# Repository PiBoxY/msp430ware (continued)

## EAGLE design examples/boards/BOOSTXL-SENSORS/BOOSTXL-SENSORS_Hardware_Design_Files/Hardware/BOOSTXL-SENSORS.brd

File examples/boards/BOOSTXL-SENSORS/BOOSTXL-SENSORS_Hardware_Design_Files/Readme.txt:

BOOSTXL-SENSORS Hardware Design Files v1.00.00
Texas Instruments, Inc.

********************************************************************************
Welcome to the BOOSTXL-SENSORS BoosterPack!
********************************************************************************

In this package, you will find hardware design files that can help you quickly
get started on developing your own project.

Available in the 'Hardware' folder are the complete board schematic and layout,
bill of material, and Gerber files.

You can also find various web links in the 'Documentation' folder pointing to
the Tool Page, Quick Start Guide, and User's Guide.

For more resources, be sure to visit www.ti.com/tool/boostxl-sensors

********************************************************************************
Revision History
********************************************************************************
Ver 1.00.00 - June 3rd, 2016
- Initial Release

********************************************************************************
Project File Listing
********************************************************************************
|--Documentation                      : Folder containing links to more resources
|--Hardware                           : Folder containing hardware design files,
                                        bill of material and gerber files
|--Readme.txt                         : This file

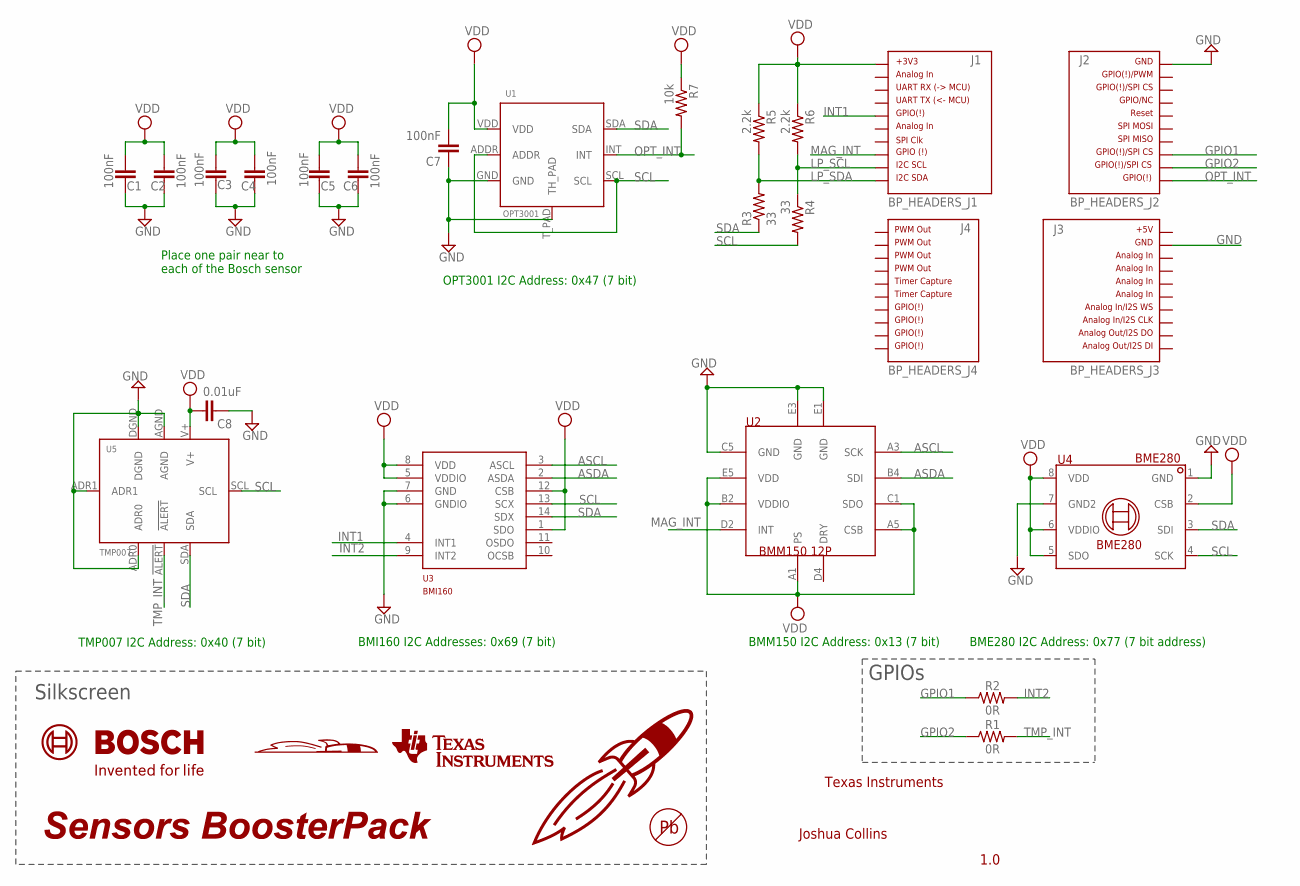
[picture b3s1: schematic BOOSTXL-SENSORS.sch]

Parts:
C1, C2, C3, C4, C5, C6, C7: 100nF; 0402-CAP
C8: 0.01uF; 0402-CAP
J1: BP_HEADERS_J1; J1
J2: BP_HEADERS_J2; J2
J3: BP_HEADERS_J3; J3
J4: BP_HEADERS_J4; J4
R1, R2: 0R; 0603
R3, R4: 33; 0402-RES
R5, R6: 2.2k; 0402-RES
R7: 10k; 0402-RES
U1: OPT3001; OPT3001DNP
U2: BMM150; WLCSP12_1.56X1.56
U3: BMI160; LGA12_2.5X3.0
U4: BME280; LGA8_2.5X2.5
U5: TMP007; TMP007AIYZF
U$1: BOSCH_LOGO_BOTTOM
U$2: HALF_ROCKET_BOTTOM_SILK; HALF_ROCKET_LG
U$3: ROCKET_45_MED_TOP_SILK
U$4: SENSORS_BP_TOP_SILK; SENSORS_BP
U$5: TI_LOGO_LG_BOTTOM_SILK; TI_LOGO_BOTTOMSILK
U$6: PB-FREE

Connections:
ASCL: U2.A3 (SCK), U3.3 (ASCL)
ASDA: U2.B4 (SDI), U3.2 (ASDA)
GND: C1.1, C2.1, C3.1, C4.1, C5.1, C6.1, C7.1, C8.1, J2.20, J3.22, U1.GND, U1.T_PAD (TH_PAD), U2.C5 (GND), U2.E1 (GND), U2.E3 (GND), U3.6 (GNDIO), U3.7 (GND), U4.1 (GND), U4.7 (GND2), U5.ADR0, U5.ADR1, U5.AGND, U5.DGND
GPIO1: J2.13, R2.1
GPIO2: J2.12, R1.1
INT1: J1.5, U3.4 (INT1)
INT2: R2.2, U3.9 (INT2)
LP_SCL: J1.9, R4.1, R6.2
LP_SDA: J1.10, R3.2, R5.2
MAG_INT: J1.8, U2.D2 (INT)
OPT_INT: J2.11, R7.2, U1.INT
SCL: R4.2, U1.ADDR, U1.SCL, U3.13 (SCX), U4.4 (SCK), U5.SCL
SDA: R3.1, U1.SDA, U3.14 (SDX), U4.3 (SDI), U5.SDA
TMP_INT: R1.2, U5.!ALERT
VDD: C1.2, C2.2, C3.2, C4.2, C5.2, C6.2, C7.2, C8.2, J1.1, R5.1, R6.1, R7.1, U1.VDD, U2.A1 (PS), U2.A5 (CSB), U2.B2 (VDDIO), U2.C1 (SDO), U2.E5 (VDD), U3.1 (SDO), U3.5 (VDDIO), U3.8 (VDD), U3.12 (CSB), U4.2 (CSB), U4.5 (SDO), U4.6 (VDDIO), U4.8 (VDD), U5.V+

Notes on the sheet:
BMI160 I2C Addresses: 0x69 (7 bit)
BMM150 I2C Address: 0x13 (7 bit)
BME280 I2C Address: 0x77 (7 bit address)
Place one pair near to each of the Bosch sensor
TMP007 I2C Address: 0x40 (7 bit)
OPT3001 I2C Address: 0x47 (7 bit)
Silkscreen
Texas Instruments
Joshua Collins
1.0
GPIOs

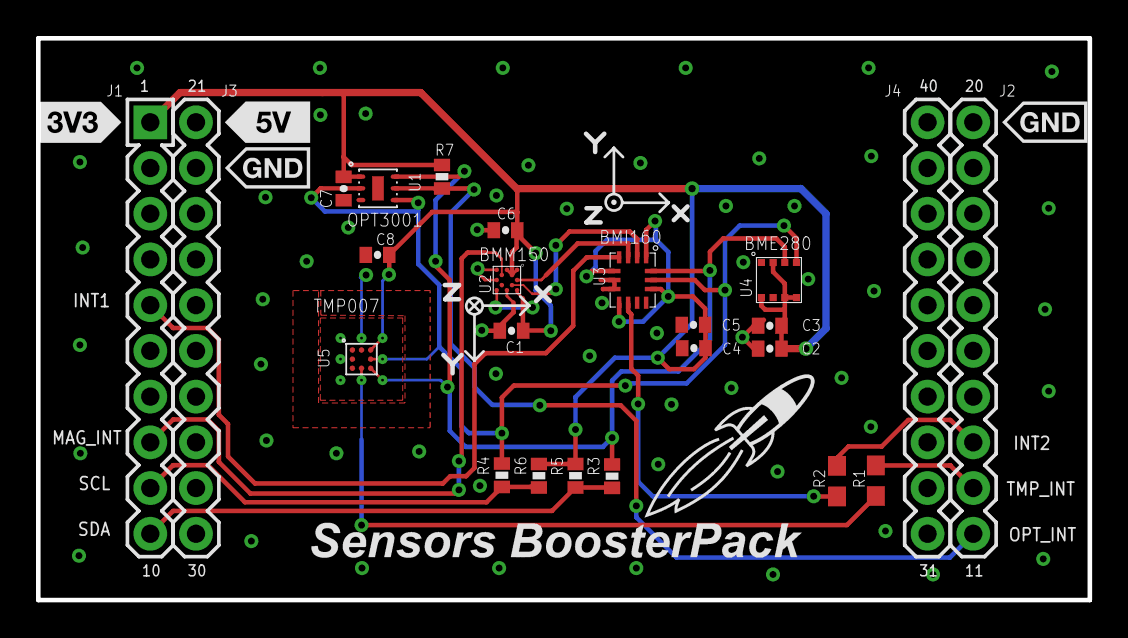
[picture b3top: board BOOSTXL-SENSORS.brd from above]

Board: 2 copper layers, 58.4 x 31.2 mm, 30 parts (0 on the bottom side), 15 nets.

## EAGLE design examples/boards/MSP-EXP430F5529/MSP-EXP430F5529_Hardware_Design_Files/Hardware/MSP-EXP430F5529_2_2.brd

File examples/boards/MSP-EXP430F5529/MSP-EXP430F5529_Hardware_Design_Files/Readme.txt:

MSP-EXP430F5529 Experimenter's Board Hardware Design Files v1.40.00
Texas Instruments, Inc.

********************************************************************************
Welcome to the MSP-EXP430F5529 Experimenter's Board!
********************************************************************************

In this package, you will find hardware design files that can help you quickly
get started on developing your own project.

Available in the 'Hardware' folder are the complete board schematic and layout,
bill of material and Gerber files.

You can also find various web links in the 'Documentation' folder pointing to
the LaunchPad's Homepage, Quick Start Guide, and User's Guide.

For more resources, be sure to visit www.ti.com/tool/msp-exp430f5529

********************************************************************************
Revision History
********************************************************************************
Ver 1.40.00 - August 24th, 2015
- Added new hardware Rev2.2 design files
- Updated User Experience demo to work with new replacement accelerometer

********************************************************************************
Project File Listing
********************************************************************************
|--Documentation                      : Folder containing links to more resources
|--Hardware                           : Folder containing hardware design files,
                                        bill of material and gerber files
|--Readme.txt                         : This file

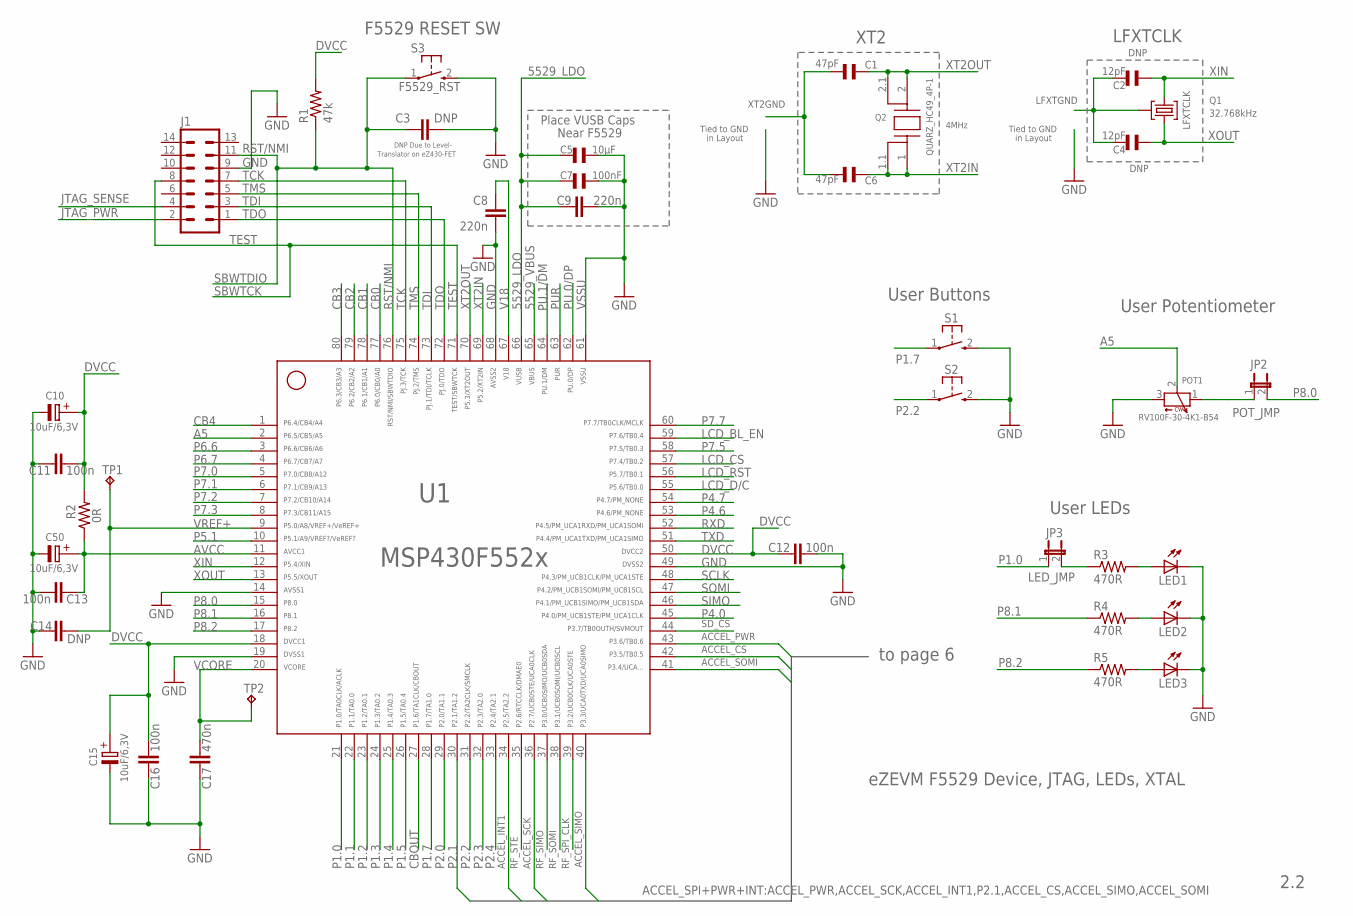
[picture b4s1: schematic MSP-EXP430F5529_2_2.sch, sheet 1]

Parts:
C1, C6: 47pF; CSMD0805
C2, C4: 12pF; CSMD0805
C3, C14: DNP; C0603
C5: 10µF; CSMD0805
C7: 100nF; CSMD0805
C8, C9: 220n; C0603
C10, C15, C50: 10uF/6,3V; 1210ELKO
C11: 100n; C0603
C12, C13, C16: 100n; C0805
C17: 470n; C0805
J1: ML14
JP2: POT_JMP; JP1S
JP3: LED_JMP; JP1S
LED1, LED2, LED3: LEDCHIPLED_0603; CHIPLED_0603
POT1: RV100F-30-4K1-B54; TW-700171
Q1: 32.768kHz; F20XX_PIR_DEMO_&_EVAL_CMJ206T
Q2: QUARZ_HC49_4P-1; QUARZ_HC49_4P
R1: 47k; R0603
R2: 0R; R0603
R3, R4, R5: 470R; R0603
S1, S2: PB; PBTH
S3: F5529_RST; PBTH
TP1, TP2: TP
U1: MSP430F5529IPNR; PN80

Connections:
5529_LDO: C5.1, C7.1, C9.1, U1.66; also elsewhere on the board
5529_VBUS: U1.65; also elsewhere on the board
A5: POT1.2 (TAP), U1.2
ACCEL_CS: U1.42; also elsewhere on the board
ACCEL_INT1: U1.34; also elsewhere on the board
ACCEL_PWR: U1.43; also elsewhere on the board
ACCEL_SCK: U1.36; also elsewhere on the board
ACCEL_SIMO: U1.40; also elsewhere on the board
ACCEL_SOMI: U1.41; also elsewhere on the board
AVCC: C13.1, C50.+, R2.1, U1.11
CB0: U1.77; also elsewhere on the board
CB1: U1.78; also elsewhere on the board
CB2: U1.79; also elsewhere on the board
CB3: U1.80; also elsewhere on the board
CB4: U1.1; also elsewhere on the board
CBOUT: U1.27; also elsewhere on the board
DVCC: C10.+, C11.2, C12.1, C15.+, C16.2, R1.2, R2.2, U1.18, U1.50; also elsewhere on the board
GND: C3.1, C5.2, C7.2, C8.2, C9.2, C10.-, C11.1, C12.2, C13.2, C14.1, C15.-, C16.1, C17.1, C50.-, J1.9, LED1.C, LED2.C, LED3.C, POT1.3 (CW), S1.2 (S), S2.2 (S), S3.2 (S), U1.14, U1.19, U1.49, U1.61, U1.68; also elsewhere on the board
JTAG_PWR: J1.2; also elsewhere on the board
JTAG_SENSE: J1.4; also elsewhere on the board
LCD_BL_EN: U1.59; also elsewhere on the board
LCD_CS: U1.57; also elsewhere on the board
LCD_D/C: U1.55; also elsewhere on the board
LCD_RST: U1.56; also elsewhere on the board
LFXTGND: C2.2, C4.2, Q1.P3 (GND)
unnamed: LED3.A, R5.2
unnamed: LED1.A, R3.2
unnamed: LED2.A, R4.2
unnamed: JP3.2, R3.1
unnamed: JP2.1, POT1.1 (CCW)
P1.0: JP3.1, U1.21; also elsewhere on the board
P1.1: U1.22; also elsewhere on the board
P1.2: U1.23; also elsewhere on the board
P1.3: U1.24; also elsewhere on the board
P1.4: U1.25; also elsewhere on the board
P1.5: U1.26; also elsewhere on the board
P1.7: S1.1, U1.28
P2.0: U1.29; also elsewhere on the board
P2.1: U1.30; also elsewhere on the board
P2.2: S2.1, U1.31
P2.3: U1.32; also elsewhere on the board
P2.4: U1.33; also elsewhere on the board
P4.0: U1.45; also elsewhere on the board
P4.6: U1.53; also elsewhere on the board
P4.7: U1.54; also elsewhere on the board
P5.1: U1.10; also elsewhere on the board
P6.6: U1.3; also elsewhere on the board
P6.7: U1.4; also elsewhere on the board
P7.0: U1.5; also elsewhere on the board
P7.1: U1.6; also elsewhere on the board
P7.2: U1.7; also elsewhere on the board
P7.3: U1.8; also elsewhere on the board
P7.5: U1.58; also elsewhere on the board
P7.7: U1.60; also elsewhere on the board
P8.0: JP2.2, U1.15; also elsewhere on the board
P8.1: R4.1, U1.16; also elsewhere on the board
P8.2: R5.1, U1.17; also elsewhere on the board
PU.0/DP: U1.62; also elsewhere on the board
PU.1/DM: U1.64; also elsewhere on the board
PUR: U1.63; also elsewhere on the board
RF_SIMO: U1.37; also elsewhere on the board
RF_SOMI: U1.38; also elsewhere on the board
RF_SPI_CLK: U1.39; also elsewhere on the board
RF_STE: U1.35; also elsewhere on the board
RST/NMI: C3.2, J1.11, R1.1, S3.1, U1.76; also elsewhere on the board
RXD: U1.52; also elsewhere on the board
SCLK: U1.48; also elsewhere on the board
SD_CS: U1.44; also elsewhere on the board
SIMO: U1.46; also elsewhere on the board
SOMI: U1.47; also elsewhere on the board
TCK: J1.7, U1.75
TDI: J1.3, U1.73
TDO: J1.1, U1.72
TEST: J1.8, U1.71; also elsewhere on the board
TMS: J1.5, U1.74
TXD: U1.51; also elsewhere on the board
V18: C8.1, U1.67
VCORE: C17.2, TP2.1, U1.20
VREF+: C14.2, TP1.1, U1.9
XIN: C2.1, Q1.P2 (2), U1.12
XOUT: C4.1, Q1.P1 (1), U1.13
XT2GND: C1.2, C6.2
XT2IN: C6.1, Q2.1, Q2.1.1, U1.69
XT2OUT: C1.1, Q2.2, Q2.2.1, U1.70

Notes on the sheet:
4MHz
eZEVM F5529 Device, JTAG, LEDs, XTAL
LFXTCLK
DNP
SBWTDIO
SBWTCK
VSSU
2.2
Place VUSB Caps
Near F5529
F5529 RESET SW
DNP Due to Level-
Translator on eZ430-FET
User LEDs
User Buttons
User Potentiometer
XT2
Tied to GND
in Layout
to page 6

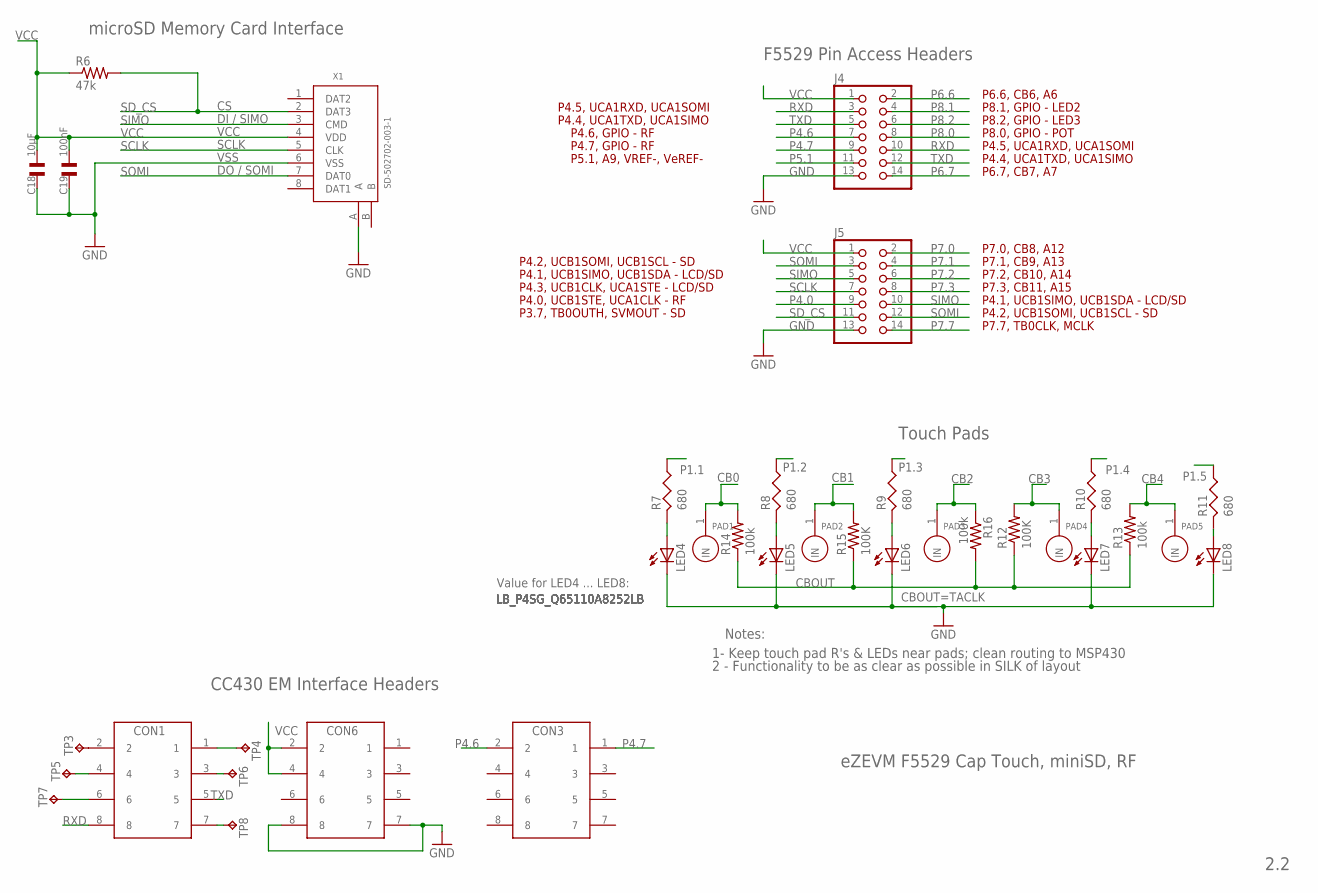
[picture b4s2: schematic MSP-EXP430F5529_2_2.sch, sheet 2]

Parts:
C18: 10µF; CSMD0805
C19: 100nF; CSMD0805
CON1, CON2, CON3: 8PIN_SM_MA_HEADER
J4, J5: PINHD-2X7; 2X07
LED4, LED5, LED6, LED7, LED8: LB_P4SG_Q65110A8252LB; LB_P4SG_Q65110A8252
PAD1, PAD2, PAD3, PAD4, PAD5: TPAD_TOPLB_P4SG; PAD_10X10_LB_P4SG
R6: 47k; R0603
R7, R8, R9, R10, R11: 680; R0805
R12, R15: 100K; R0603
R13, R14, R16: 100k; R0603
TP3, TP4, TP5, TP6, TP7, TP8: TP
X1: SD-502702-003-1; SD-502702-003

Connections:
CB0: PAD1.1, R14.2; also elsewhere on the board
CB1: PAD2.1, R15.2; also elsewhere on the board
CB2: PAD3.1, R16.1; also elsewhere on the board
CB3: PAD4.1, R12.2; also elsewhere on the board
CB4: PAD5.1, R13.2; also elsewhere on the board
CBOUT: R12.1, R13.1, R14.1, R15.1, R16.2; also elsewhere on the board
GND: C18.1, C19.1, CON2.7, CON2.8, J4.13, J5.13, LED4.C, LED5.C, LED6.C, LED7.C, LED8.C, X1.6 (VSS), X1.A; also elsewhere on the board
unnamed: LED7.A, R10.2
unnamed: LED5.A, R8.2
unnamed: LED6.A, R9.2
unnamed: LED4.A, R7.2
unnamed: CON1.6, TP7.1
unnamed: LED8.A, R11.2
unnamed: CON1.4, TP5.1
unnamed: CON1.2, TP3.1
unnamed: CON1.1, TP4.1
unnamed: CON1.3, TP6.1
unnamed: CON1.7, TP8.1
P1.1: R7.1; also elsewhere on the board
P1.2: R8.1; also elsewhere on the board
P1.3: R9.1; also elsewhere on the board
P1.4: R10.1; also elsewhere on the board
P1.5: R11.1; also elsewhere on the board
P4.0: J5.9; also elsewhere on the board
P4.6: CON3.2, J4.7; also elsewhere on the board
P4.7: CON3.1, J4.9; also elsewhere on the board
P5.1: J4.11; also elsewhere on the board
P6.6: J4.2; also elsewhere on the board
P6.7: J4.14; also elsewhere on the board
P7.0: J5.2; also elsewhere on the board
P7.1: J5.4; also elsewhere on the board
P7.2: J5.6; also elsewhere on the board
P7.3: J5.8; also elsewhere on the board
P7.7: J5.14; also elsewhere on the board
P8.0: J4.8; also elsewhere on the board
P8.1: J4.4; also elsewhere on the board
P8.2: J4.6; also elsewhere on the board
RXD: CON1.8, J4.3, J4.10; also elsewhere on the board
SCLK: J5.7, X1.5 (CLK); also elsewhere on the board
SD_CS: J5.11, R6.2, X1.2 (DAT3); also elsewhere on the board
SIMO: J5.5, J5.10, X1.3 (CMD); also elsewhere on the board
SOMI: J5.3, J5.12, X1.7 (DAT0); also elsewhere on the board
TXD: CON1.5, J4.5, J4.12; also elsewhere on the board
VCC: C18.2, C19.2, CON2.2, CON2.4, J4.1, J5.1, R6.1, X1.4 (VDD); also elsewhere on the board

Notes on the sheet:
eZEVM F5529 Cap Touch, miniSD, RF
CON1
CON3
CON6
CC430 EM Interface Headers
microSD Memory Card Interface
DI / SIMO
DO / SOMI
SCLK
VCC
VSS
2.2
Touch Pads
Notes:
1- Keep touch pad R's & LEDs near pads; clean routing to MSP430
2 - Functionality to be as clear as possible in SILK of layout
CBOUT=TACLK
F5529 Pin Access Headers
P7.0, CB8, A12
P7.1, CB9, A13
P7.2, CB10, A14
P7.3, CB11, A15
P4.1, UCB1SIMO, UCB1SDA - LCD/SD
P7.7, TB0CLK, MCLK
P8.1, GPIO - LED2
P8.2, GPIO - LED3
P4.5, UCA1RXD, UCA1SOMI
P6.7, CB7, A7
P4.4, UCA1TXD, UCA1SIMO
P5.1, A9, VREF-, VeREF-
P4.6, GPIO - RF
P4.7, GPIO - RF
P4.3, UCB1CLK, UCA1STE - LCD/SD
P4.2, UCB1SOMI, UCB1SCL - SD
P4.0, UCB1STE, UCA1CLK - RF
P3.7, TB0OUTH, SVMOUT - SD
P6.6, CB6, A6
P8.0, GPIO - POT
Value for LED4 ... LED8:

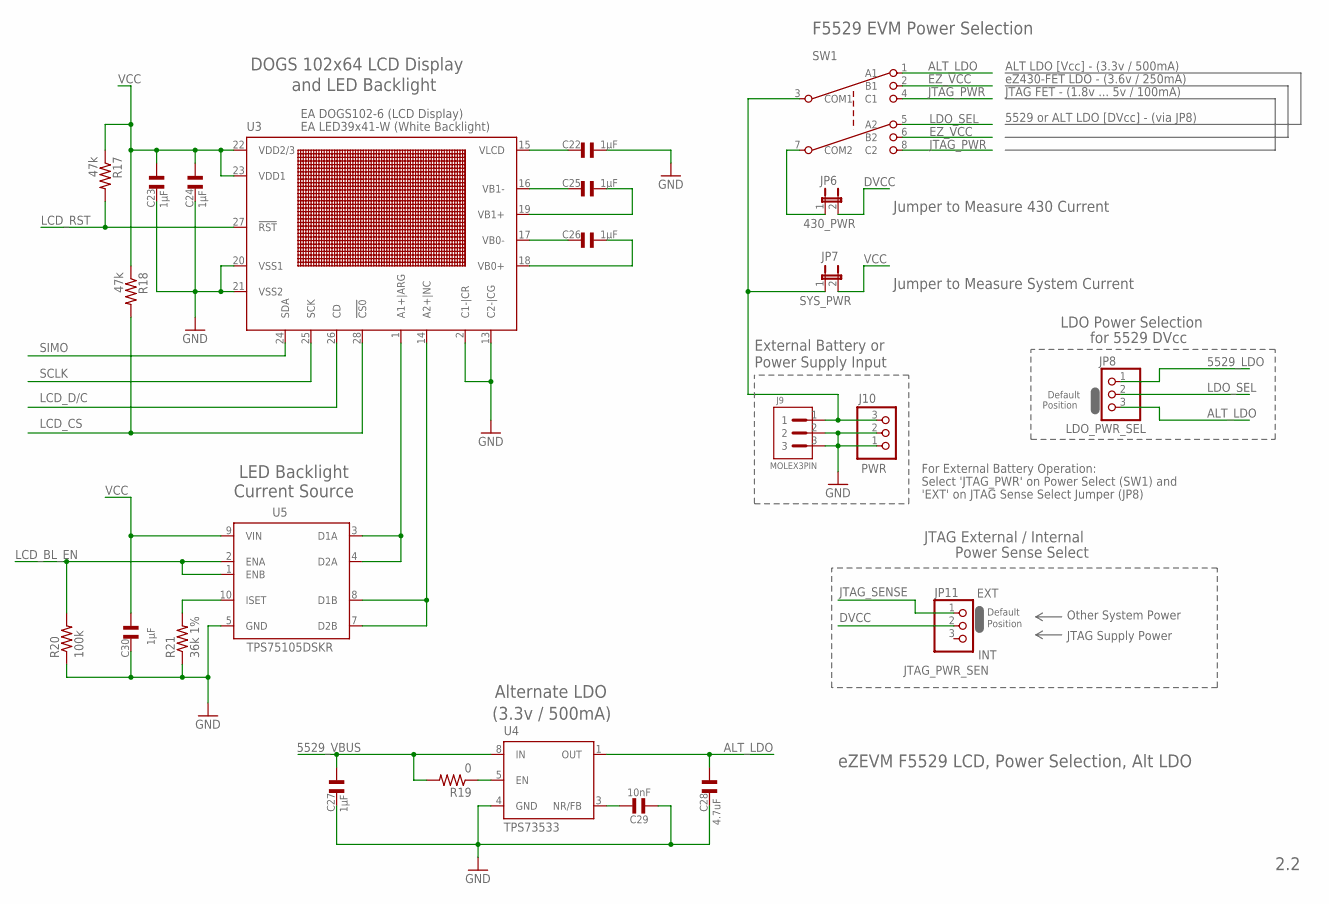
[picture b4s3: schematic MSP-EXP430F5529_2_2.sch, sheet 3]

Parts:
C22, C23, C24, C25, C26, C27, C30: 1µF; CSMD0805
C28: 4.7uF; CSMD0805
C29: 10nF; CSMD0805
J9: MOLEX3PIN; MOLEX-3P-HEADER
J10: PWR; 1X03
JP6: 430_PWR; JP1
JP7: SYS_PWR; JP1
JP8: LDO_PWR_SEL; 1X03S
JP11: JTAG_PWR_SEN; 1X03S
R17, R18: 47k; R0603
R19: 0; R0603
R20: 100k; R0603
R21: 36k 1%; R0603
SW1: 3PDT
U3: EA DOGS102-6 (LCD Display); EADOGS102-6
U4: TPS73533; DRB_S-PVSON-N8
U5: TPS75105DSKR; DSK_S-PDSO-N10

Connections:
5529_LDO: JP8.1; also elsewhere on the board
5529_VBUS: C27.2, R19.2, U4.8 (IN); also elsewhere on the board
ALT_LDO: C28.2, JP8.3, SW1.1 (A1), U4.1 (OUT)
D1A: U3.1 (A1+|ARG), U5.3 (D1A), U5.4 (D2A)
D1B: U3.14 (A2+|NC), U5.7 (D2B), U5.8 (D1B)
DVCC: JP6.2, JP11.2; also elsewhere on the board
DVCC_SW: JP6.1, SW1.7 (COM2)
EZ_VCC: SW1.2 (B1), SW1.6 (B2); also elsewhere on the board
GND: C22.2, C23.1, C24.1, C27.1, C28.1, C29.1, C30.1, J9.2, J9.3, J10.1, J10.2, R20.1, R21.1, U3.2 (C1-|CR), U3.13 (C2-|CG), U3.20 (VSS1), U3.21 (VSS2), U4.2 (GND), U4.4 (GND), U4.6 (GND), U4.7 (GND), U4.PP@1 (GND), U4.PP@2 (GND), U4.PP@3 (GND), U4.PP@4 (GND), U4.PP@5 (GND), U4.TH (GND), U4.TH@1 (GND), U4.TH@2 (GND), U5.5 (GND), U5.P$1 (GND), U5.P$2 (GND), U5.P$3 (GND), U5.P$4 (GND), U5.P$5 (GND), U5.PP (GND); also elsewhere on the board
ISET: R21.2, U5.10 (ISET)
JTAG_PWR: SW1.4 (C1), SW1.8 (C2); also elsewhere on the board
JTAG_SENSE: JP11.1; also elsewhere on the board
LCD_BL_EN: R20.2, U5.1 (ENB), U5.2 (ENA); also elsewhere on the board
LCD_CS: R18.2, U3.28 (!CS0); also elsewhere on the board
LCD_D/C: U3.26 (CD); also elsewhere on the board
LCD_RST: R17.2, U3.27 (!RST); also elsewhere on the board
LDO_SEL: JP8.2, SW1.5 (A2)
unnamed: R19.1, U4.5 (EN)
unnamed: C25.1, U3.16 (VB1-)
unnamed: C25.2, U3.19 (VB1+)
unnamed: C26.1, U3.17 (VB0-)
unnamed: C26.2, U3.18 (VB0+)
unnamed: C29.2, U4.3 (NR/FB)
SCLK: U3.25 (SCK); also elsewhere on the board
SIMO: U3.24 (SDA); also elsewhere on the board
VCC: C23.2, C24.2, C30.2, JP7.2, R17.1, R18.1, U3.22 (VDD2/3), U3.23 (VDD1), U5.9 (VIN); also elsewhere on the board
VCC_SW: J9.1, J10.3, JP7.1, SW1.3 (COM1)
VLCD: C22.1, U3.15 (VLCD)

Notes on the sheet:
2.2
eZEVM F5529 LCD, Power Selection, Alt LDO
DOGS 102x64 LCD Display
LED Backlight
and LED Backlight
Current Source
JTAG FET - (1.8v ... 5v / 100mA)
ALT LDO [Vcc] - (3.3v / 500mA)
eZ430-FET LDO - (3.6v / 250mA)
INT
EXT
Power Supply Input
F5529 EVM Power Selection
Alternate LDO
(3.3v / 500mA)
LDO Power Selection
Default
External Battery or
JTAG External / Internal
Power Sense Select
Position
For External Battery Operation:
Select 'JTAG_PWR' on Power Select (SW1) and
'EXT' on JTAG Sense Select Jumper (JP8)
5529 or ALT LDO [DVcc] - (via JP8)
EA LED39x41-W (White Backlight)
JTAG Supply Power
Other System Power
for 5529 DVcc
Jumper to Measure 430 Current
Jumper to Measure System Current

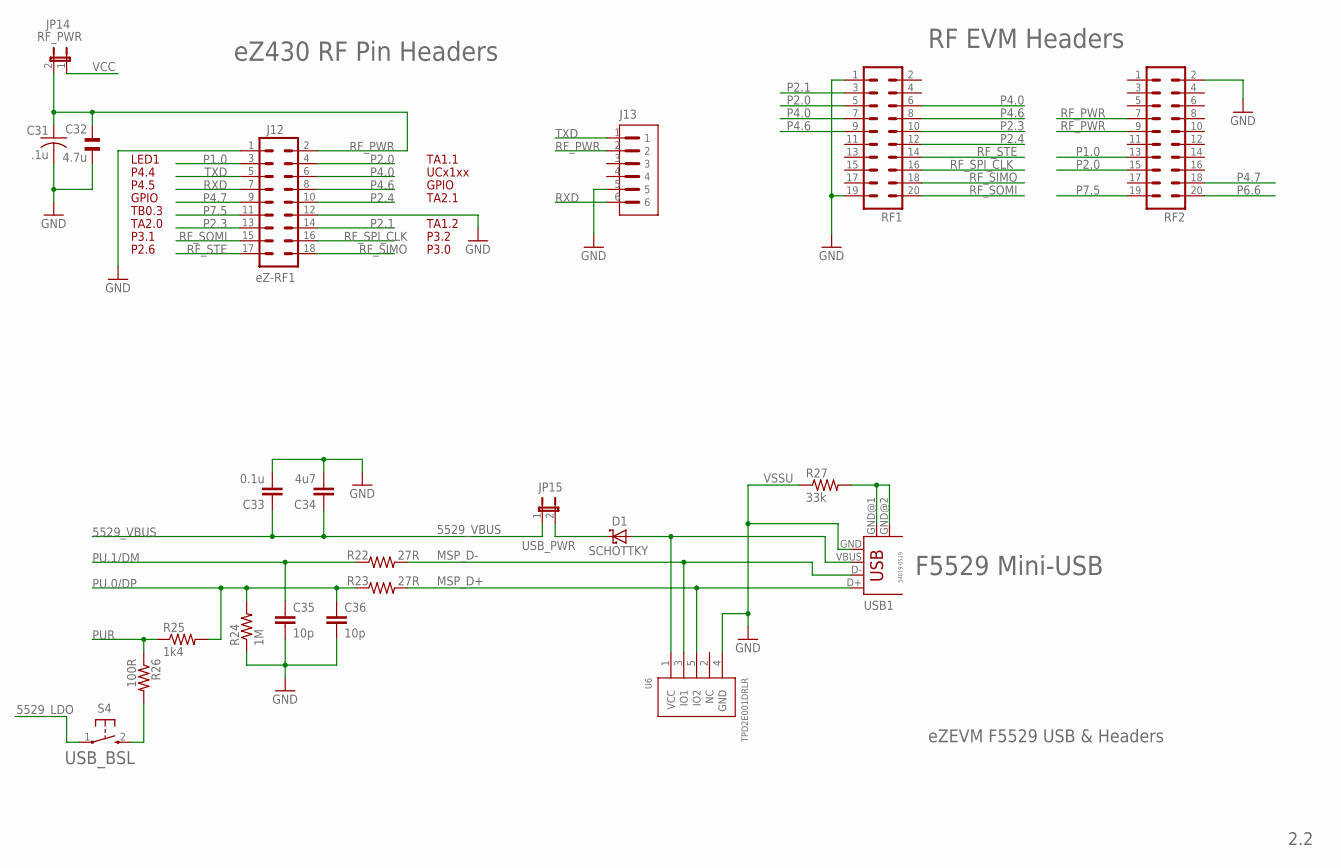
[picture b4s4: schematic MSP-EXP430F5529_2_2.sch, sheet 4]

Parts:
C31: .1u; C0603
C32: 4.7u; CSMD0805
C33: 0.1u; C0603
C34: 4u7; C0603
C35, C36: 10p; C0603
D1: SCHOTTKY; MINIMELF
J12: eZ-RF1; _MSP430_RF_MA09-2
J13: eZRF; SL127L6
JP14: RF_PWR; JP1
JP15: USB_PWR; JP1
R22, R23: 27R; R0603
R24: 1M; R0603
R25: 1k4; R0603
R26: 100R; R0603
R27: 33k; R0603
RF1, RF2: TFM-110-02-SM-D-A-K
S4: USB_BSL; PBTH
U6: TPD2E001DRLR; TPD2E001-DRL
USB1: F5529 Mini-USB; USB-MB-H

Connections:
5529_LDO: S4.1; also elsewhere on the board
5529_VBUS: C33.1, C34.1, JP15.1; also elsewhere on the board
GND: C31.2, C32.2, C33.2, C34.2, C35.2, C36.2, J12.1, J12.12, J13.5, R24.1, R27.1, RF1.1, RF1.19, RF2.2, U6.4 (GND), USB1.GND; also elsewhere on the board
MSP_D+: R23.2, U6.5 (IO2), USB1.D+
MSP_D-: R22.2, U6.3 (IO1), USB1.D-
unnamed: D1.C, JP15.2
unnamed: R27.2, USB1.GND@1 (GND), USB1.GND@2 (GND)
unnamed: R26.2, S4.2 (S)
unnamed: D1.A, U6.1 (VCC), USB1.VBUS
P1.0: J12.3, RF2.13; also elsewhere on the board
P2.0: J12.4, RF1.5, RF2.15; also elsewhere on the board
P2.1: J12.14, RF1.3; also elsewhere on the board
P2.3: J12.13, RF1.10; also elsewhere on the board
P2.4: J12.10, RF1.12; also elsewhere on the board
P4.0: J12.6, RF1.6, RF1.7; also elsewhere on the board
P4.6: J12.8, RF1.8, RF1.9; also elsewhere on the board
P4.7: J12.9, RF2.18; also elsewhere on the board
P6.6: RF2.20; also elsewhere on the board
P7.5: J12.11, RF2.19; also elsewhere on the board
PU.0/DP: C36.1, R23.1, R24.2, R25.2; also elsewhere on the board
PU.1/DM: C35.1, R22.1; also elsewhere on the board
PUR: R25.1, R26.1; also elsewhere on the board
RF_PWR: C31.1, C32.1, J12.2, J13.2, JP14.2, RF2.7, RF2.9
RF_SIMO: J12.18, RF1.18; also elsewhere on the board
RF_SOMI: J12.15, RF1.20; also elsewhere on the board
RF_SPI_CLK: J12.16, RF1.16; also elsewhere on the board
RF_STE: J12.17, RF1.14; also elsewhere on the board
RXD: J12.7, J13.6; also elsewhere on the board
TXD: J12.5, J13.1; also elsewhere on the board
VCC: JP14.1; also elsewhere on the board

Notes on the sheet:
VSSU
2.2
eZEVM F5529 USB & Headers
RF EVM Headers
eZ430 RF Pin Headers
54819-0519
GPIO
TA1.2
TA1.1
UCx1xx
TA2.1
P3.2
P3.0
P4.5
TB0.3
LED1
P4.4
TA2.0
P3.1
P2.6

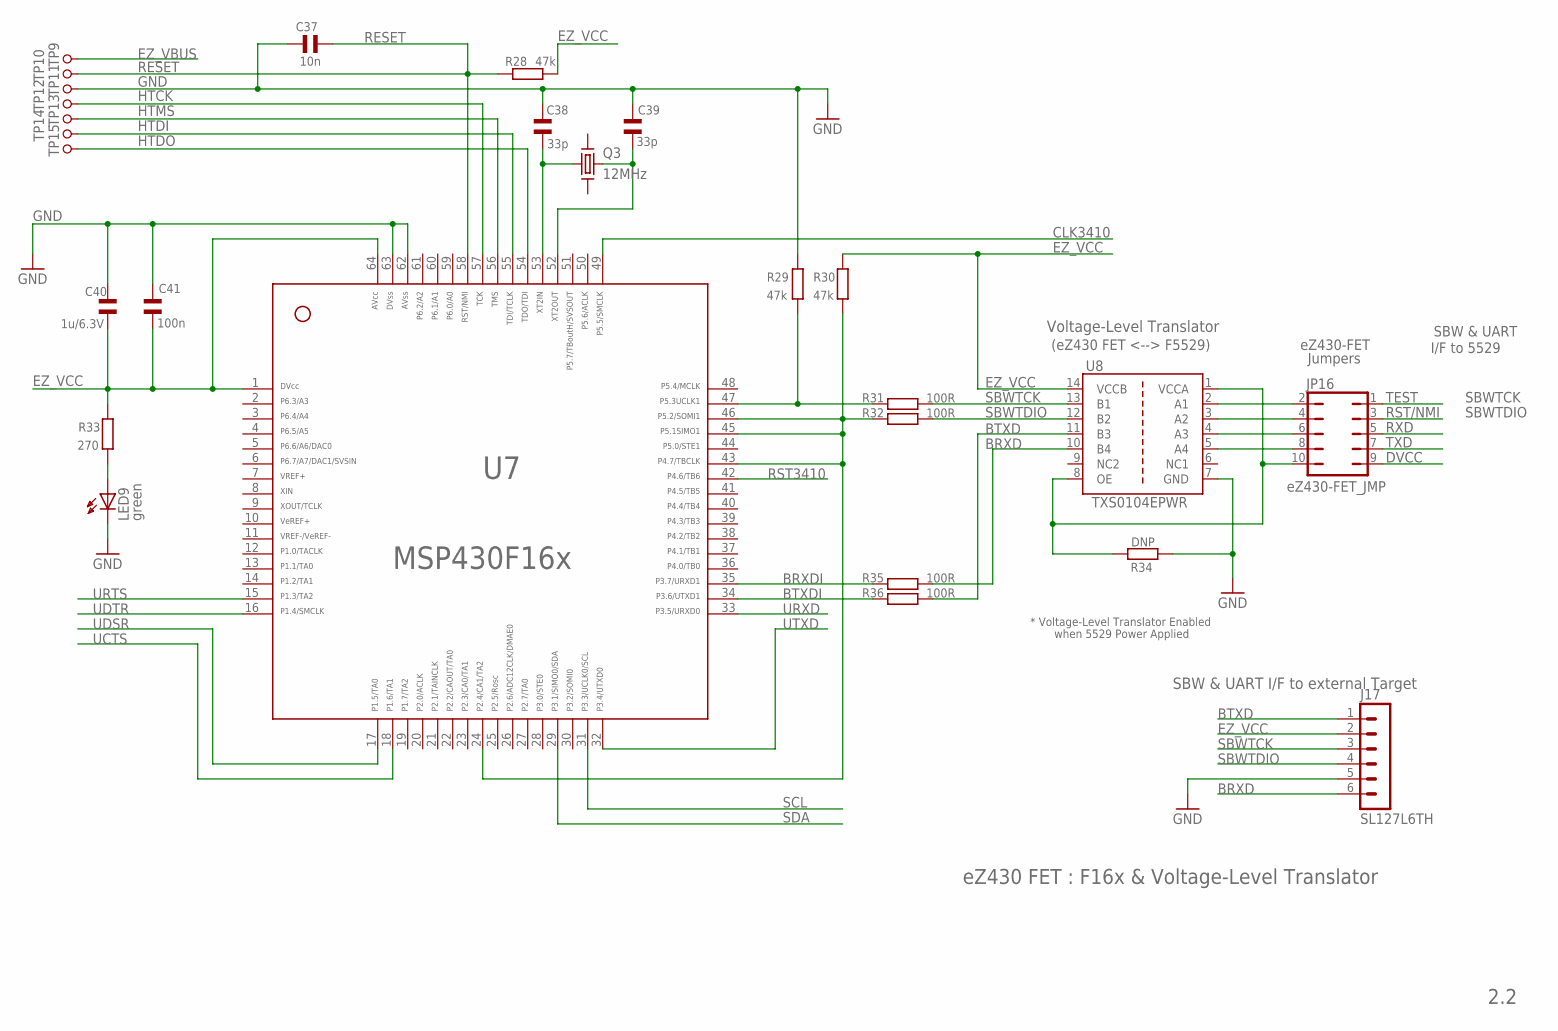
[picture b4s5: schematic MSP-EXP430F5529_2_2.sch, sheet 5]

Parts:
C37: 10n; 0402
C38, C39: 33p; 0402
C40: 1u/6.3V; 0603
C41: 100n; 0402
J17: SL127L6TH; SL127L6_MPE
JP16: eZ430-FET_JMP; JP5Q
LED9: green; DIODE0603
Q3: 12MHz; FT10A
R28, R29, R30: 47k; 0402
R31, R32, R35, R36: 100R; 0402
R33: 270; 0402
R34: DNP; 0402
TP9, TP10, TP11, TP12, TP13, TP14, TP15: TP05TP10; TP10
U7: MSP430F1612IPMR; PM/PAG64
U8: TXS0104EPWR; PW_R-PDSO-G14

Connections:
BRXD: J17.6, R35.2, U8.10 (B4)
BRXDI: R35.1, U7.35; also elsewhere on the board
BTXD: J17.1, R36.2, U8.11 (B3)
BTXDI: R36.1, U7.34; also elsewhere on the board
CLK3410: U7.49; also elsewhere on the board
DVCC: JP16.9; also elsewhere on the board
EZ_VBUS: TP9.1; also elsewhere on the board
EZ_VCC: C40.2, C41.1, J17.2, R28.2, R30.2, R33.2, U7.1, U7.64, U8.14 (VCCB); also elsewhere on the board
GND: C37.2, C38.2, C39.2, C40.1, C41.2, J17.5, LED9.K (C), R29.2, R34.1, TP11.1, U7.62, U7.63, U8.7 (GND); also elsewhere on the board
HTCK: TP12.1, U7.57
HTDI: TP14.1, U7.55
HTDO: TP15.1, U7.54
HTMS: TP13.1, U7.56
unnamed: R29.1, R31.1, U7.47
unnamed: R30.1, R32.1, U7.24, U7.43, U7.45, U7.46
unnamed: JP16.2, U8.2 (A1)
unnamed: LED9.A, R33.1
unnamed: JP16.4, U8.3 (A2)
unnamed: JP16.6, U8.4 (A3)
unnamed: JP16.8, U8.5 (A4)
unnamed: JP16.10, R34.2, U8.1 (VCCA), U8.8 (OE)
RESET: C37.1, R28.1, TP10.1, U7.58; also elsewhere on the board
RST3410: U7.42; also elsewhere on the board
RST/NMI: JP16.3; also elsewhere on the board
RXD: JP16.5; also elsewhere on the board
SBWTCK: J17.3, R31.2, U8.13 (B1)
SBWTDIO: J17.4, R32.2, U8.12 (B2)
SCL: U7.31; also elsewhere on the board
SDA: U7.29; also elsewhere on the board
TEST: JP16.1; also elsewhere on the board
TXD: JP16.7; also elsewhere on the board
UCTS: U7.18; also elsewhere on the board
UDSR: U7.17; also elsewhere on the board
UDTR: U7.16; also elsewhere on the board
URTS: U7.15; also elsewhere on the board
URXD: U7.33; also elsewhere on the board
UTXD: U7.32; also elsewhere on the board
XIN1: C39.1, Q3.P$3 (3), U7.52
XOUT1: C38.1, Q3.P$1 (1), U7.53

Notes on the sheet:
eZ430 FET : F16x & Voltage-Level Translator
2.2
SBW & UART I/F to external Target
SBW & UART
eZ430-FET
Voltage-Level Translator
(eZ430 FET <--> F5529)
Jumpers
I/F to 5529
* Voltage-Level Translator Enabled
when 5529 Power Applied
SBWTDIO
SBWTCK

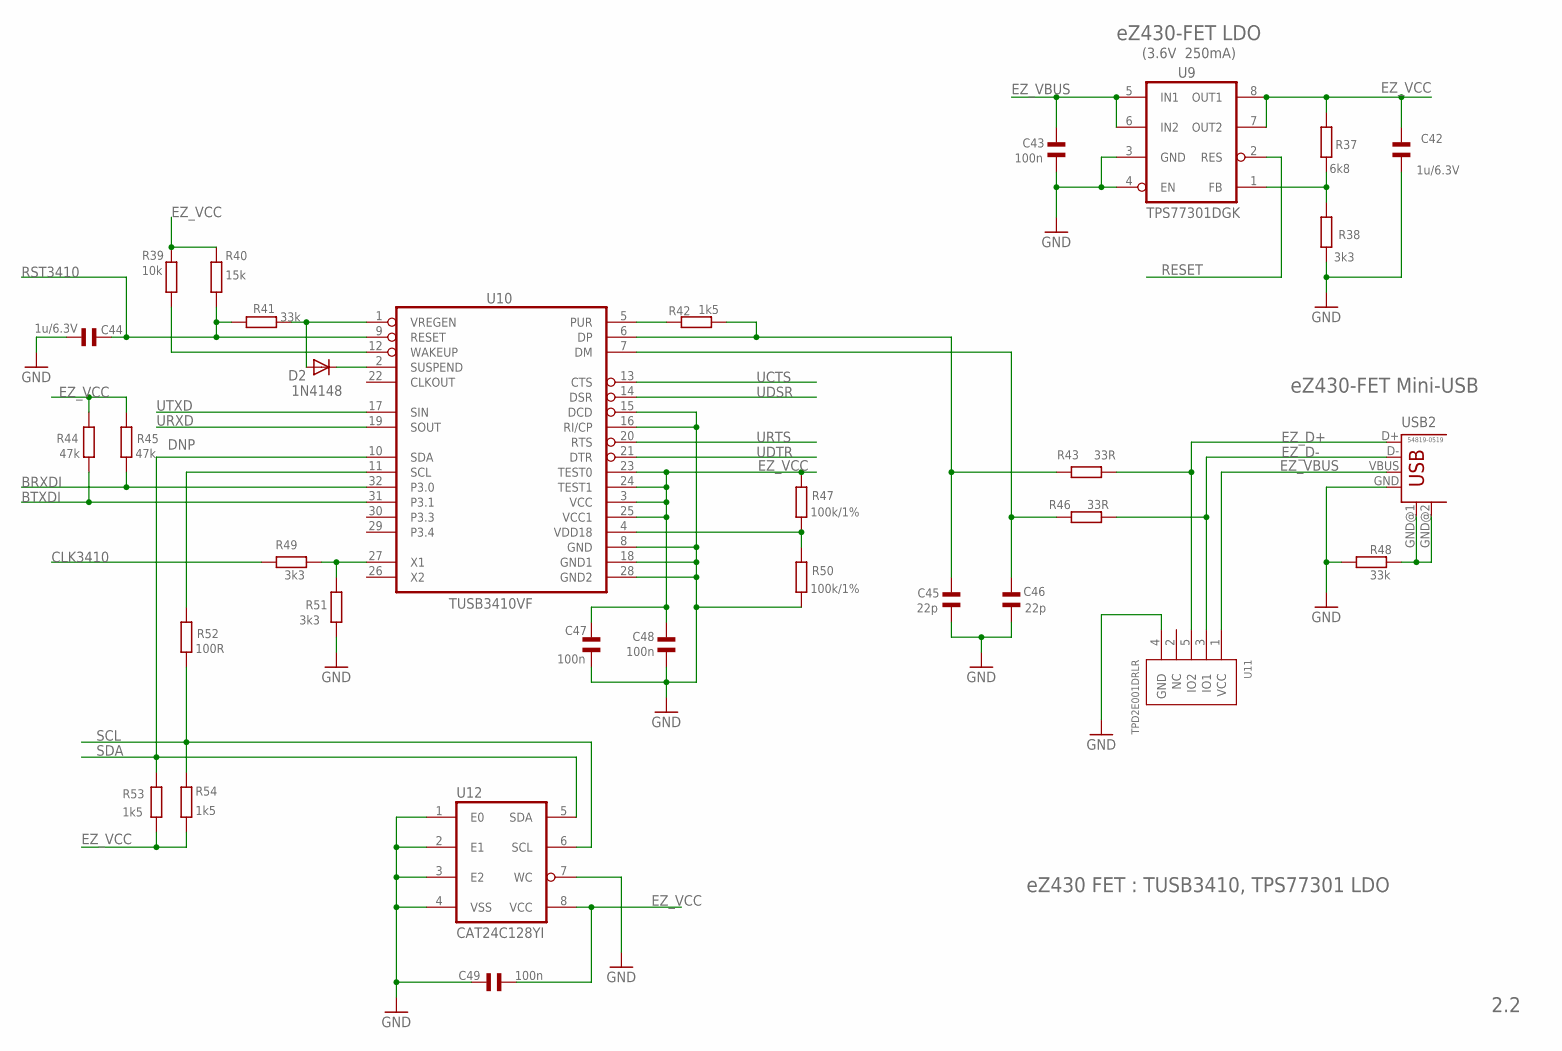
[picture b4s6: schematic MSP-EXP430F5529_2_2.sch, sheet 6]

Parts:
C42, C44: 1u/6.3V; 0603
C43, C47, C48, C49: 100n; 0402
C45, C46: 22p; 0402
D2: 1N4148; SOD110-R
R37: 6k8; 0402
R38, R49, R51: 3k3; 0402
R39: 10k; 0402
R40: 15k; 0402
R41, R48: 33k; 0402
R42, R53, R54: 1k5; 0402
R43, R46: 33R; 0402
R44, R45: 47k; 0402
R47, R50: 100k/1%; 0402
R52: 100R; 0402
U9: TPS77301DGK; MSOP8
U10: TUSB3410VF; QFP32
U11: TPD2E001DRLR; TPD2E001-DRL
U12: CAT24C128YI; USBFET_TSSOP8
USB2: eZ430-FET Mini-USB; USB-MB-H

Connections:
BRXDI: R45.1, U10.32 (P3.0); also elsewhere on the board
BTXDI: R44.1, U10.31 (P3.1); also elsewhere on the board
CLK3410: R49.2; also elsewhere on the board
EZ_D+: R43.1, U11.5 (IO2), USB2.D+
EZ_D-: R46.1, U11.3 (IO1), USB2.D-
EZ_VBUS: C43.2, U9.5 (IN1), U9.6 (IN2), U11.1 (VCC), USB2.VBUS; also elsewhere on the board
EZ_VCC: C42.1, C47.2, C48.2, C49.1, R37.2, R39.2, R40.2, R44.2, R45.2, R47.2, R53.1, R54.1, U9.7 (OUT2), U9.8 (OUT1), U10.3 (VCC), U10.23 (TEST0), U10.24 (TEST1), U10.25 (VCC1), U12.8 (VCC); also elsewhere on the board
GND: C42.2, C43.1, C44.2, C45.1, C46.1, C47.1, C48.1, C49.2, R38.1, R48.1, R50.1, R51.2, U9.3 (GND), U9.4 (EN), U10.8 (GND), U10.15 (DCD), U10.16 (RI/CP), U10.18 (GND1), U10.28 (GND2), U11.4 (GND), U12.1 (E0), U12.2 (E1), U12.3 (E2), U12.4 (VSS), U12.7 (WC), USB2.GND; also elsewhere on the board
unnamed: R49.1, R51.1, U10.27 (X1)
unnamed: R37.1, R38.2, U9.1 (FB)
unnamed: D2.A, R41.1, U10.1 (VREGEN)
unnamed: D2.C, U10.2 (SUSPEND)
unnamed: R39.1, U10.12 (WAKEUP)
unnamed: R52.2, U10.11 (SCL)
unnamed: R47.1, R50.2, U10.4 (VDD18)
unnamed: R48.2, USB2.GND@1 (GND), USB2.GND@2 (GND)
unnamed: R42.2, U10.5 (PUR)
unnamed: C46.2, R46.2, U10.7 (DM)
unnamed: C45.2, R42.1, R43.2, U10.6 (DP)
RESET: U9.2 (RES); also elsewhere on the board
RST3410: C44.1, R40.1, R41.2, U10.9 (RESET); also elsewhere on the board
SCL: R52.1, R54.2, U12.6 (SCL); also elsewhere on the board
SDA: R53.2, U10.10 (SDA), U12.5 (SDA); also elsewhere on the board
UCTS: U10.13 (CTS); also elsewhere on the board
UDSR: U10.14 (DSR); also elsewhere on the board
UDTR: U10.21 (DTR); also elsewhere on the board
URTS: U10.20 (RTS); also elsewhere on the board
URXD: U10.19 (SOUT); also elsewhere on the board
UTXD: U10.17 (SIN); also elsewhere on the board

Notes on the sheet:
eZ430 FET : TUSB3410, TPS77301 LDO
2.2
DNP
eZ430-FET LDO
(3.6V 250mA)
54819-0519
